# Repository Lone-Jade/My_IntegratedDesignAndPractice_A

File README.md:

# AI_TCRT5000 — 文字识别器提交归档（STM32G0B1 + 8 路 TCRT5000）

基于《综合实验》任务书的**文字识别器**项目：用 **8 个 TCRT5000 红外反射传感器**排成一条直线，通过**定时器分时驱动 + ADC 采集**扫描纸片上的数字字符，数据经 **USB 串口**上送 PC；PC 端重建图像并训练识别模型，模型经 **ST Edge AI 量化为 int8** 部署到板载 **STM32G0B1RBT6**，扫描完成后**直接在单片机上推理**，结果经 **LED 数码管显示**（置信度≥30%，保持 5s）并通过串口输出 0-9 各数字概率。

本仓库为按开发阶段整理的**提交归档**：每个目录是一份独立快照（含必要依赖，可单独使用），供提交/存档/评审使用。

---

## 1. 系统概览

```mermaid
flowchart TD
    SEN["8×TCRT5000 反射传感器<br/>U1..U8 直线排列"] --> MCU

    subgraph MCU["STM32G0B1RBT6（64MHz）"]
        TIM["TIM6 2ms 节拍<br/>更新中断驱动"]
        DRV["分时驱动<br/>逐路点亮 LED[n]：PD0..PD6/PD8"]
        ADC["ADC1 单通道转换<br/>PA0..PA7 逐路切换"]
        UART["USART1 115200<br/>21B 二进制帧 + [AI] 结果行"]
        AI["板载推理<br/>ST Edge AI int8 网络<br/>（ai_scan.c）"]
        SEG["LED 数码管<br/>PB0-PB7 共阴"]
        TIM --> DRV --> ADC
        ADC --> UART
        UART --> AI
        AI --> SEG
    end

    UART -->|"USB 串口"| PC

    subgraph PC["PC 端 Python 工具"]
        SCAN["scan_view.py<br/>采集 + 自动分段 → *.csv"]
        PRT["make_print_sheet(_fonts).py<br/>打印稿生成（MNIST / 10 种字体）"]
        TRN["train_digit.py<br/>PyTorch CNN 训练 + 集成"]
        QNT["quantize_onnx.py<br/>int8 QDQ 量化"]
        AIE["stedgeai validate<br/>生成 C 模型 + 验证"]
        SHOW["show_prediction.py<br/>板载概率显示"]
        SCAN --> TRN
        TRN --> QNT --> AIE --> AI
        SHOW --> UART
    end
```

| 环节   | 方案                                                                                       |
| ------ | ------------------------------------------------------------------------------------------ |
| 传感器 | 8×TCRT5000（反射式红外），同一时刻仅 1 路发射管点亮（分时，消除串扰/低功耗）              |
| 采集   | ADC1 单通道转换（Scan Disabled），`HAL_ADC_ConfigChannel` 逐路切换；采样时间 79.5 cycles |
| 节拍   | TIM6 2ms（CubeMX 配置：PSC=64-1, Period=1999），更新中断驱动                               |
| 传输   | USART1 115200，二进制帧 21B（行号 + 8×u16 + 校验和），一行 8 通道 = 16ms ≈ 62.5 行/秒    |
| 推理   | ST Edge AI int8 网络（权重 22.4KB、激活 8KB），扫描完成自动板载推理                        |
| 显示   | 单 LED 数码管（PB0-PB7 共阴），置信度 ≥30% 显示预测数字并保持 5s                          |

---

## 2. 仓库结构

```text
My_IntegratedDesignAndPractice_A/
├── README.md                              # 仓库总览（本文件）
│
├── AI_TCRT5000_ScanData/                  # 扫描部分（第一阶段，已完成 ✅）
│   ├── Core/                              # 采集固件：TIM6 分时驱动 + ADC + 串口二进制帧
│   └── Drivers/  cmake/  *.ioc  *.ld  startup*.s   
│
├── Dataset/                               # 最新数据集：0-9 各 30 个 = 300 个扫描 CSV
│   └── datasets/<digit>_scan/             # <digit>-NN.csv（01-20 MNIST 打印体 / 21-30 标准字体）
│
├── Model_v1/                              # 第一版模型（历史存档，200 样本、随机 14/3/3）
│   ├── python/                            # 训练/预处理/量化/导出/检查脚本
│   ├── c/                                 # ST Edge AI int8 C 模型（Network/）+ 运行时
│   └── artifacts/                         # 模型产物、训练曲线/混淆矩阵、可行性测试报告
│
├── Model_v2/                              # 最新版模型（部署，300 样本、固定 20/5/5）
│   ├── python/                            # 训练/评估/预处理/量化/导出/检查脚本
│   ├── c/                                 # 第二轮 int8 C 模型（generate-2）+ 运行时
│   └── artifacts/                         # 部署模型、int8 ONNX、划分清单、报告与图片
│
├── Python_Tools/                          # 最新 Python 工具链（12 个）
│   └── tools/                             # 采集/渲染/打印稿/训练/评估/体检/量化/验证/显示
│
├── AI_TCRT5000_CHAR_RECOGNITION/          # 最新单片机工程（采集 + 板载推理 + 数码管，可构建）
│   ├── Core/                              # main.c / ai_scan.c / seg_display.c 等
│   ├── Network/                           # ST Edge AI int8 网络（5 个文件）
│   ├── Middlewares/ST/AI/                 # ST Edge AI 运行时（头文件 + CM0+ 运行库）
│   └── *.ioc  cmake/  CMakeLists.txt  ... # CubeMX 工程与 CMake 构建/调试配置
│
├── Kicad/                                 # 硬件电路：原理图 + PCB（KiCad 工程 AI_PCB_SCH）
│   └── AI_PCB_SCH.kicad_{pro,sch,pcb,dru,prl}
│
└── video/                                 # 演示视频与结果
    ├── 测试视频.mp4                       # 实测演示（可在Relesaes查看）
    └── results.xlsx                       # 结果汇总表
```

---

## 3. 各目录详解

### 3.1 AI_TCRT5000_ScanData — 扫描部分（第一阶段）

数据采集阶段快照：

- `Core/`：采集固件（`main.c` 分时驱动 / ADC 采集 / 二进制帧组帧；tim/adc/usart/gpio 由 CubeMX 生成）
- `Drivers/ cmake/ *.ioc *.ld startup`：CubeMX 工程与 CMake 构建配置
- `docs/`：`Question.md`（任务书）、`传感器测试_任务书.md`、`传感器测试_电路连接说明.md`

### 3.2 Dataset — 数据集（300 样本）

`datasets/<digit>_scan/<digit>-NN.csv`：数字 0-9 各 30 个，共 **300 个扫描样本**。

- 每文件 = 一张独立纸片的一次扫描（8 通道 ADC 原始值 0-4095；白纸=低值、黑墨=高值），行格式 `row,ch0..ch7`，行数 22-118（人工扫描快慢不同）；
- 命名：`NN = 01-20` 为 **MNIST 打印体**，`21-30` 为 **10 种标准字体**（DejaVu/Liberation/URW/C059 等，`make_print_sheet_fonts.py` 生成打印稿后扫描）；
- **固定划分**（新旧字体按比例混入各集合）：训练 = 1-14 + 21-26、验证 = 15-17 + 27-28、测试 = 18-20 + 29-30（每类 20/5/5），划分清单见 `Model_v2/artifacts/split_fixed.json`；
- 质量复检：`Python_Tools/tools/check_samples.py`（黑边/墨量/截断/留出误判分析）。

### 3.3 Model_v1 — 第一版模型（历史存档）

200 样本、**随机 14/3/3** 划分：

- `python/`：`train_digit.py`（PyTorch 微型 CNN 22.6k 参数 + LS/WD + 集成 + ONNX 导出）、`preprocess.py`、`quantize_onnx.py`、`export_ai_studio_data.py`、`check_samples.py`
- `c/`：ST Edge AI 生成的 int8 C 模型（`Network/`）+ 运行时（`Middlewares/ST/AI/`）
- `artifacts/`：`model_best.pt`/`model_final.pt`、`model.onnx`/`model_best_int8.onnx`、`ai_studio_test.npz`、`summary_{baseline,enhanced,ensemble}.json`、`training_log.csv`、`curves.png`/`confusion_matrix.png`、`识别可行性测试报告.md`
- 结果：基线 **75.3%±4.0%** → LS+WD **81.3%±6.5%**（5 划分）、多 seed 投票 **83.3%**；部署模型测试 **76.67%**（30 样本），int8 与 float32 均 76.67%（零精度损失）。

### 3.4 Model_v2 — 最新版模型（部署）

300 样本、**固定划分 20/5/5**：

- `python/`：`train_digit.py`（`--split fixed` + LS/WD + 5 seed 集成 + ONNX 导出）、`preprocess.py`、`eval_model.py`、`check_samples.py`、`export_ai_studio_data.py`、`quantize_onnx.py`
- `c/`：**第二轮 `stedgeai generate-2` 生成的 int8 网络**（`Network/`，权重 22,928B）+ 运行时（`Middlewares/ST/AI/`）
- `artifacts/`：`model_best.pt`（部署模型 seed 1042）、`model_final.pt`、`models_seed{42,1042,2042,3042,4042}.pt`（5 个集成模型）、`model.onnx`/`model_best.onnx`/`model_best_int8.onnx`、`ai_studio_test.npz`、`split_fixed.json`、`summary_fixed_repeats.json`/`summary_fixed_ensemble.json`/`train_summary.json`、`training_log.csv`、`curves.png`/`confusion_matrix.png`/`preprocess_grid.png`、`识别可行性测试报告.md`（含第一轮 §1-§9 与第二轮 §10-§11）
- 结果：5 seed 测试 **81.2%±1.0%**、多数投票 **88.0%**；部署模型测试 **82.0%**（50 样本）；新字体（域外）识别 **94%**；int8 零精度损失（stedgeai validate：rmse=0、nse=1.0、cos=1.0）。

### 3.5 Python_Tools — 工具链（12 个）

最新版全套工具链：

| 工具                          | 功能                                                                            |
| ----------------------------- | ------------------------------------------------------------------------------- |
| `scan_view.py`              | 串口采集 + 按"数据恢复 4095"自动分段，每字符存一个 CSV                          |
| `show_scan.py`              | CSV 渲染颜色深度图（`--thresh` 纯黑白二值化）                                 |
| `make_print_sheet.py`       | MNIST 打印稿生成（反色 + 加粗 + A4 排版；torchvision/gz 双数据源）              |
| `make_print_sheet_fonts.py` | **字体版打印稿生成**（10 种系统标准字体，编号 x-21-x-30）                 |
| `check_quality.py`          | 扫描 CSV 质量体检（早期版本）                                                   |
| `preprocess.py`             | 预处理管线：无纸电平黑边 v2 裁剪 + 固定高度重采样（32×8）+ 逐样本归一化 + 增强 |
| `train_digit.py`            | PyTorch 微型 CNN 训练 0-9（固定划分 + LS/WD + 多 seed 集成 + ONNX 导出）        |
| `eval_model.py`             | 用已训练模型评估指定扫描集（新数据复测）                                        |
| `check_samples.py`          | 样本质量体检 + 留出误判分析（建议重扫清单）                                     |
| `export_ai_studio_data.py`  | 导出 ST Edge AI 验证 .npz（x_test + one-hot y_test，形状 (N,1,1,10)）           |
| `quantize_onnx.py`          | ONNX int8 QDQ 静态量化（→ model_best_int8.onnx）                               |
| `show_prediction.py`        | 串口监听，解析`[AI]` 概率行，终端条形图显示预测 + 历史                        |

依赖：numpy / torch(CPU) / matplotlib / pyserial / onnx / onnxruntime（按需）。

### 3.6 AI_TCRT5000_CHAR_RECOGNITION — 最新单片机工程（部署固件）

当前完整固件，可构建（第二轮 int8 固件）：

- `Core/Src/main.c`：采样主循环（TIM6 分时驱动 + ADC 采集 + 二进制帧上送）
- `Core/Src/ai_scan.c`：**板载 AI 模块**——扫描缓冲/结束检测、预处理（黑边裁剪→重采样 32 行→归一化→int8 量化）、`stai_network_run` 推理、softmax、串口概率输出、数码管驱动
- `Core/Src/seg_display.c`：单 LED 数码管驱动（PB0-PB7 共阴）
- `Network/`：ST Edge AI 生成的 int8 网络（2026-08-27 generate-2，权重 22.4KB）
- `Middlewares/ST/AI/`：ST Edge AI 运行时（头文件 + CM0+ 运行库）
- `AI_TCRT5000_CHAR_RECOGNITION.ioc`、`Drivers/`、`cmake/`、`CMakeLists.txt`、`CMakePresets.json`、`startup_stm32g0b1xx.s`、`STM32G0B1xx_FLASH.ld`：CubeMX 工程与 CMake 构建/调试配置
- 资源占用：**Flash 53.10%**（69604 B / 128 KB）、**RAM 12.04%**（17752 B / 144 KB）

> **模型更新说明**：更换模型只需替换 `Network/` 下全部 5 个文件（`network.c/h`、`network_data.c/h`、`network_details.h`），`ai_scan.c` 无需改动（API 不变，输出反量化 scale 由 `network.h` 的 `STAI_NETWORK_OUT_1_SCALE` 宏自动更新）。

### 3.7 Kicad — 硬件电路（原理图 + PCB）

KiCad 工程 `AI_PCB_SCH`（最新版），与单片机工程配套的硬件设计：

- `AI_PCB_SCH.kicad_pro`：KiCad 工程文件
- `AI_PCB_SCH.kicad_sch`：原理图
- `AI_PCB_SCH.kicad_pcb`：PCB 版图
- `AI_PCB_SCH.kicad_dru`：设计规则
- `AI_PCB_SCH.kicad_prl`：工程本地设置（KiCad 自动生成，通常不纳入版本管理）

---

## 4. 关键结果

### 4.1 第一版 vs 最新版对比

| 指标                    | Model_v1（200 样本，随机 14/3/3） | Model_v2（300 样本，固定 20/5/5） |
| ----------------------- | --------------------------------- | --------------------------------- |
| 测试集规模              | 30 样本                           | 50 样本                           |
| 单模型测试均值          | 81.3% ± 6.5%                     | 81.2% ± 1.0%                     |
| 多数投票（PC 端）       | 83.3%                             | **88.0%**                   |
| 部署模型测试            | 76.67%                            | **82.0%**                   |
| 新字体（域外）识别      | 16% / 52%                         | **94%**                     |
| int8 部署精度损失       | 零                                | 零                                |
| 固件资源（Flash / RAM） | 53.1% / 12.0%                     | 53.10% / 12.04%                   |

### 4.2 关键结论

- **采集链路完整可用**：8 路传感器读数正常（白纸=低值 -764-1500，黑墨=高值 -4095）；实测扫描 96 行/字符，帧同步/校验和/自动分段全部验证通过；
- **PC 识别训练可行**：固定划分（新旧字体混合）5 seed 重复实验测试 **81.2%±1.0%**，多 seed 投票 **88.0%**；
- **字体域偏移已解决**：旧模型（仅 MNIST 打印体训练）识别新字体版样本仅 **16%（0-4）/ 52%（5-9）**；固定划分新旧字体混合重训后，部署模型对新字体样本识别率 **94%**；
- **板载部署验证通过**：int8 量化零精度损失（权重 22.4KB、激活 8KB），`stedgeai validate` 50 样本 **82.0%**，C 模型与参考模型数值一致（rmse=0、nse=1.0、cos=1.0）；固件 Flash 53.10% / RAM 12.04%；
- 完整测试报告见 `Model_v2/artifacts/识别可行性测试报告.md`。

---

## 5. 快速开始

### 5.1 固件构建与烧录（Linux，需 arm-none-eabi-gcc + cmake + ninja）

```bash
cd AI_TCRT5000_CHAR_RECOGNITION
cmake --preset Debug && cmake --build --preset Debug
openocd -f interface/stlink.cfg -f target/stm32g0x.cfg \
        -c "program build/Debug/AI_TCRT5000_CHAR_RECOGNITION.elf verify reset exit"
```

### 5.2 采集字符数据（PC）

```bash
pip install pyserial
python3 Python_Tools/tools/scan_view.py /dev/ttyUSB0 --image   # 或 Windows: ... COM3
```

操作：扫一个字符 → 拿开纸片等数据恢复 4095 → 扫下一个；CSV 自动存入 `outputs/`。

### 5.3 训练与评估（PC）

```bash
python3 Model_v2/python/train_digit.py --split fixed --repeats 5    # 固定划分重复实验
python3 Model_v2/python/train_digit.py --split fixed --ensemble 5   # 多 seed 投票 + ONNX 导出（部署模型）
python3 Model_v2/python/eval_model.py --digits 0-4 --seq 21-30      # 用已保存模型评估新字体样本（复测）
```

### 5.4 ST Edge AI 验证与 int8 量化（PC）

```bash
python3 Model_v2/python/export_ai_studio_data.py    # 生成验证数据 ai_studio_test.npz
python3 Model_v2/python/quantize_onnx.py            # ONNX int8 量化 → model_best_int8.onnx
stedgeai validate --model <int8.onnx> --valinput <ai_studio_test.npz> \
  --classifier --mode host --name network --target stm32g0 --workspace <ws> --output <out>
# 生成的 C 代码替换 AI_TCRT5000_CHAR_RECOGNITION/Network/（见 §3.6 模型更新说明）
```

### 5.5 查看板载推理结果（PC）

```bash
python3 Python_Tools/tools/show_prediction.py /dev/ttyUSB0
```

烧录板载 AI 固件后，扫描数字并拿开纸片，终端即显示 10 类概率条形图与最近历史。

---

## 6. 串口协议

一行 = 一次 8 通道采样（21 字节二进制帧）：

```
[0xAA][0x55][行号 u16 LE][CH0..CH7 × u16 LE][校验和 u8]     共 21 字节
校验和 = 字节 2..19 之和 & 0xFF
```

- 行号自增，相邻行间隔 16ms（TIM6 2ms × 8 路）；极性：白纸=低值、黑墨=高值。

每次扫描结束（纸片离开），固件另输出一行**板载推理结果**（文本，与二进制帧共存）：

```
[AI] rows=56 best=9:94% | 0:0% 1:0% 2:0% 3:0% 4:0% 5:1% 6:0% 7:0% 8:5% 9:94%
```

`rows` = 扫描行数（裁剪前），`best` = 置信最高数字，其后为 0-9 的预测概率（整数百分比）。

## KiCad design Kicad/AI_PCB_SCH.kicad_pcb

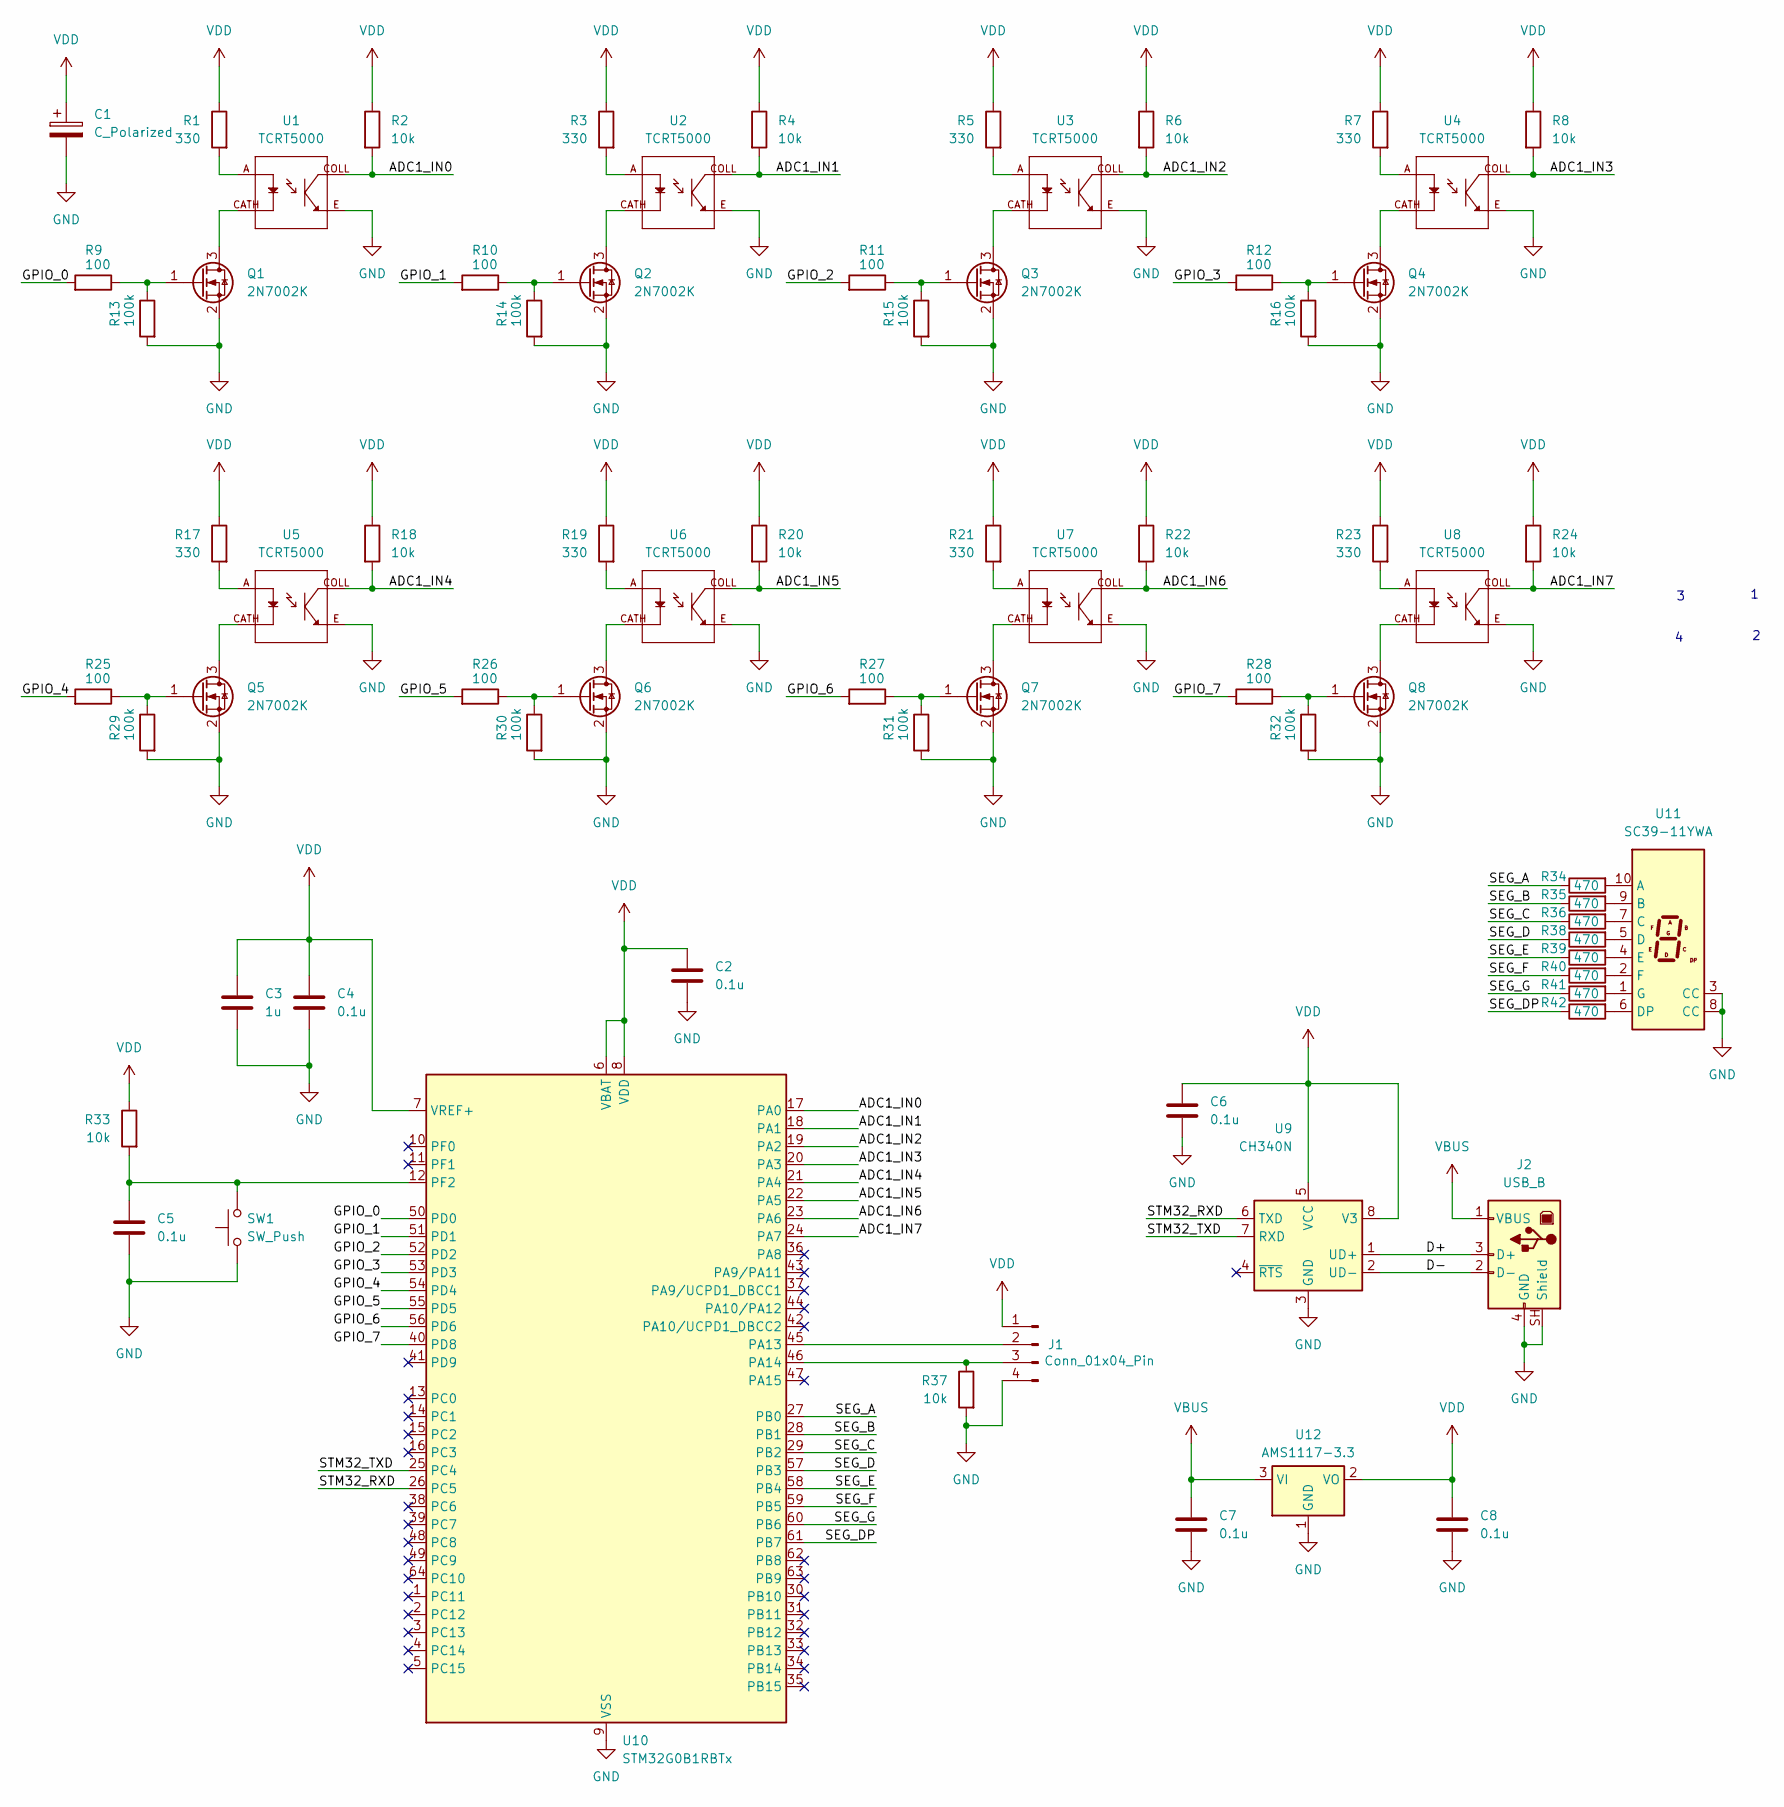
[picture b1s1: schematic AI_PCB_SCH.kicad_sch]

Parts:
C1: C_Polarized; CP_Radial_D5.0mm_P2.00mm
C2, C4, C5, C6, C7, C8: 0.1u; C_0805_2012Metric_Pad1.18x1.45mm_HandSolder
C3: 1u; C_0805_2012Metric_Pad1.18x1.45mm_HandSolder
J1: Conn_01x04_Pin; PinHeader_1x04_P2.54mm_Vertical
J2: USB_B; USB_B_Lumberg_2411_02_Horizontal
Q1, Q2, Q3, Q4, Q5, Q6, Q7, Q8: 2N7002K; SOT-23_Handsoldering
R1, R3, R5, R7, R17, R19, R21, R23: 330; R_0805_2012Metric_Pad1.20x1.40mm_HandSolder
R2, R4, R6, R8, R18, R20, R22, R24, R33, R37: 10k; R_0805_2012Metric_Pad1.20x1.40mm_HandSolder
R9, R10, R11, R12, R25, R26, R27, R28: 100; R_0805_2012Metric_Pad1.20x1.40mm_HandSolder
R13, R14, R15, R16, R29, R30, R31, R32: 100k; R_0805_2012Metric_Pad1.20x1.40mm_HandSolder
R34, R35, R36, R38, R39, R40, R41, R42: 470; R_0805_2012Metric_Pad1.20x1.40mm_HandSolder
SW1: SW_Push; SW_PUSH_6mm
U1, U2, U3, U4, U5, U6, U7, U8: TCRT5000; OPTO_TCRT5000; PARTREV 1.7
U9: CH340N; JEITA_SOIC-8_3.9x4.9mm_P1.27mm
U10: STM32G0B1RBTx; LQFP-64_10x10mm_P0.5mm
U11: SC39-11YWA; Sx39-1xxxxx
U12: AMS1117-3.3; SOT-223-3_TabPin2

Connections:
/ADC1_IN0: R2.2, U1.COLL, U10.17 (PA0)
/ADC1_IN1: R4.2, U2.COLL, U10.18 (PA1)
/ADC1_IN2: R6.2, U3.COLL, U10.19 (PA2)
/ADC1_IN3: R8.2, U4.COLL, U10.20 (PA3)
/ADC1_IN4: R18.2, U5.COLL, U10.21 (PA4)
/ADC1_IN5: R20.2, U6.COLL, U10.22 (PA5)
/ADC1_IN6: R22.2, U7.COLL, U10.23 (PA6)
/ADC1_IN7: R24.2, U8.COLL, U10.24 (PA7)
/D+: J2.3 (D+), U9.1 (UD+)
/D-: J2.2 (D-), U9.2 (UD-)
/GPIO_0: R9.2, U10.50 (PD0)
/GPIO_1: R10.2, U10.51 (PD1)
/GPIO_2: R11.2, U10.52 (PD2)
/GPIO_3: R12.2, U10.53 (PD3)
/GPIO_4: R25.2, U10.54 (PD4)
/GPIO_5: R26.2, U10.55 (PD5)
/GPIO_6: R27.2, U10.56 (PD6)
/GPIO_7: R28.2, U10.40 (PD8)
/SEG_A: R34.1, U10.27 (PB0)
/SEG_B: R35.1, U10.28 (PB1)
/SEG_C: R36.1, U10.29 (PB2)
/SEG_D: R38.1, U10.57 (PB3)
/SEG_DP: R42.1, U10.61 (PB7)
/SEG_E: R39.1, U10.58 (PB4)
/SEG_F: R40.1, U10.59 (PB5)
/SEG_G: R41.1, U10.60 (PB6)
/STM32_RXD: U9.6 (TXD), U10.26 (PC5)
/STM32_TXD: U9.7 (RXD), U10.25 (PC4)
GND: C1.2, C2.2, C3.2, C4.2, C5.2, C6.2, C7.2, C8.2, J1.4, J2.4 (GND), J2.SH (Shield), Q1.2 (S), Q2.2 (S), Q3.2 (S), Q4.2 (S), Q5.2 (S), Q6.2 (S), Q7.2 (S), Q8.2 (S), R13.2, R14.2, R15.2, R16.2, R29.2, R30.2, R31.2, R32.2, R37.2, SW1.1, U1.E, U2.E, U3.E, U4.E, U5.E, U6.E, U7.E, U8.E, U9.3 (GND), U10.9 (VSS), U11.3 (CC), U11.8 (CC), U12.1 (GND)
unnamed: J1.2, U10.45 (PA13)
unnamed: J1.3, R37.1, U10.46 (PA14)
unnamed: Q1.3 (D), U1.CATH
unnamed: Q1.1 (G), R9.1, R13.1
unnamed: Q2.3 (D), U2.CATH
unnamed: Q2.1 (G), R10.1, R14.1
unnamed: Q3.3 (D), U3.CATH
unnamed: Q3.1 (G), R11.1, R15.1
unnamed: Q4.3 (D), U4.CATH
unnamed: Q4.1 (G), R12.1, R16.1
unnamed: Q5.3 (D), U5.CATH
unnamed: Q5.1 (G), R25.1, R29.1
unnamed: Q6.3 (D), U6.CATH
unnamed: Q6.1 (G), R26.1, R30.1
unnamed: Q7.3 (D), U7.CATH
unnamed: Q7.1 (G), R27.1, R31.1
unnamed: Q8.3 (D), U8.CATH
unnamed: Q8.1 (G), R28.1, R32.1
unnamed: R1.2, U1.A
unnamed: R3.2, U2.A
unnamed: R5.2, U3.A
unnamed: R7.2, U4.A
unnamed: R17.2, U5.A
unnamed: R19.2, U6.A
unnamed: R21.2, U7.A
unnamed: R23.2, U8.A
unnamed: C5.1, R33.2, SW1.2, U10.12 (PF2)
unnamed: R34.2, U11.10 (A)
unnamed: R35.2, U11.9 (B)
unnamed: R36.2, U11.7 (C)
unnamed: R38.2, U11.5 (D)
unnamed: R42.2, U11.6 (DP)
unnamed: R39.2, U11.4 (E)
unnamed: R40.2, U11.2 (F)
unnamed: R41.2, U11.1 (G)
VBUS: C7.1, J2.1 (VBUS), U12.3 (VI)
VDD: C1.1, C2.1, C3.1, C4.1, C6.1, C8.1, J1.1, R1.1, R2.1, R3.1, R4.1, R5.1, R6.1, R7.1, R8.1, R17.1, R18.1, R19.1, R20.1, R21.1, R22.1, R23.1, R24.1, R33.1, U9.5 (VCC), U9.8 (V3), U10.6 (VBAT), U10.7 (VREF+), U10.8 (VDD), U12.2 (VO)

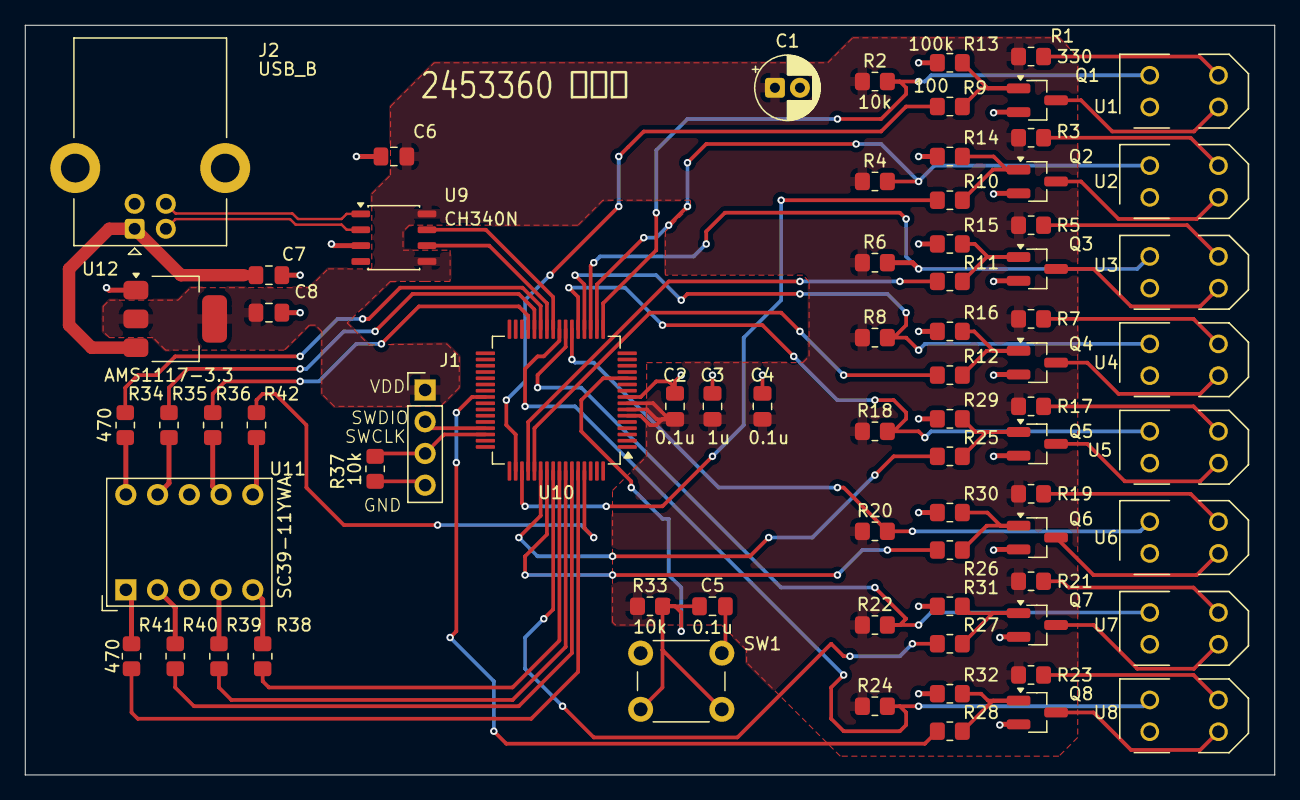
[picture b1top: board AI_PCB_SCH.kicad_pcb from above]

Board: 2 copper layers, 100.0 x 60.0 mm, 73 parts (0 on the bottom side), 66 nets.

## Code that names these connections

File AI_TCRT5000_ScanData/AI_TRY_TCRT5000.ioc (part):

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Mcu.Name=STM32G0B1R(B-C-E)Tx
Mcu.Package=LQFP64
Mcu.UserName=STM32G0B1RCTx
PA0.Mode=IN0
PA0.Signal=ADC1_IN0
PA1.Mode=IN1
PA1.Signal=ADC1_IN1
PA13.Mode=Serial_Wire
PA13.Signal=SYS_SWDIO
PA14-BOOT0.Mode=Serial_Wire
PA14-BOOT0.Signal=SYS_SWCLK
PA2.Mode=IN2
PA2.Signal=ADC1_IN2
PA3.Mode=IN3
PA3.Signal=ADC1_IN3
PA4.Mode=IN4
PA4.Signal=ADC1_IN4
PA5.Mode=IN5
PA5.Signal=ADC1_IN5
PA6.Mode=IN6
PA6.Signal=ADC1_IN6
PA7.Mode=IN7
PA7.Signal=ADC1_IN7
PC4.Mode=Asynchronous
PC4.Signal=USART1_TX
PC5.Mode=Asynchronous
PC5.Signal=USART1_RX
PD0.GPIOParameters=GPIO_Label
PD0.GPIO_Label=GPIO_0
PD0.Signal=GPIO_Output
PD1.GPIOParameters=GPIO_Label
PD1.GPIO_Label=GPIO_1
PD1.Signal=GPIO_Output
PD2.GPIOParameters=GPIO_Label
PD2.GPIO_Label=GPIO_2
PD2.Signal=GPIO_Output
PD3.GPIOParameters=GPIO_Label
PD3.GPIO_Label=GPIO_3
PD3.Signal=GPIO_Output
PD4.GPIOParameters=GPIO_Label
PD4.GPIO_Label=GPIO_4
PD4.Signal=GPIO_Output
PD5.GPIOParameters=GPIO_Label
PD5.GPIO_Label=GPIO_5
PD5.Signal=GPIO_Output
PD6.GPIOParameters=GPIO_Label
PD6.GPIO_Label=GPIO_6
PD6.Signal=GPIO_Output
PD8.GPIOParameters=GPIO_Label
PD8.GPIO_Label=GPIO_7
PD8.Signal=GPIO_Output
RCC.HSE_VALUE=8000000
RCC.SYSCLKFreq_VALUE=64000000
RCC.SYSCLKSource=RCC_SYSCLKSOURCE_PLLCLK
board=custom

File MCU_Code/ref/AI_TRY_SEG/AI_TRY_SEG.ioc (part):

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Mcu.Name=STM32G0B1R(B-C-E)Tx
Mcu.Package=LQFP64
Mcu.UserName=STM32G0B1RBTx
PA13.Mode=Serial_Wire
PA13.Signal=SYS_SWDIO
PA14-BOOT0.Mode=Serial_Wire
PA14-BOOT0.Signal=SYS_SWCLK
PB0.GPIOParameters=GPIO_Label
PB0.GPIO_Label=SEG_A
PB0.Signal=GPIO_Output
PB1.GPIOParameters=GPIO_Label
PB1.GPIO_Label=SEG_B
PB1.Signal=GPIO_Output
PB2.GPIOParameters=GPIO_Label
PB2.GPIO_Label=SEG_C
PB2.Signal=GPIO_Output
PB3.GPIOParameters=GPIO_Label
PB3.GPIO_Label=SEG_D
PB3.Signal=GPIO_Output
PB4.GPIOParameters=GPIO_Label
PB4.GPIO_Label=SEG_E
PB4.Signal=GPIO_Output
PB5.GPIOParameters=GPIO_Label
PB5.GPIO_Label=SEG_F
PB5.Signal=GPIO_Output
PB6.GPIOParameters=GPIO_Label
PB6.GPIO_Label=SEF_G
PB6.Signal=GPIO_Output
PB7.GPIOParameters=GPIO_Label
PB7.GPIO_Label=SEG_DP
PB7.Signal=GPIO_Output
PC4.Mode=Asynchronous
PC4.Signal=USART1_TX
PC5.Mode=Asynchronous
PC5.Signal=USART1_RX
RCC.HSE_VALUE=8000000
RCC.SYSCLKFreq_VALUE=64000000
RCC.SYSCLKSource=RCC_SYSCLKSOURCE_PLLCLK
board=custom
